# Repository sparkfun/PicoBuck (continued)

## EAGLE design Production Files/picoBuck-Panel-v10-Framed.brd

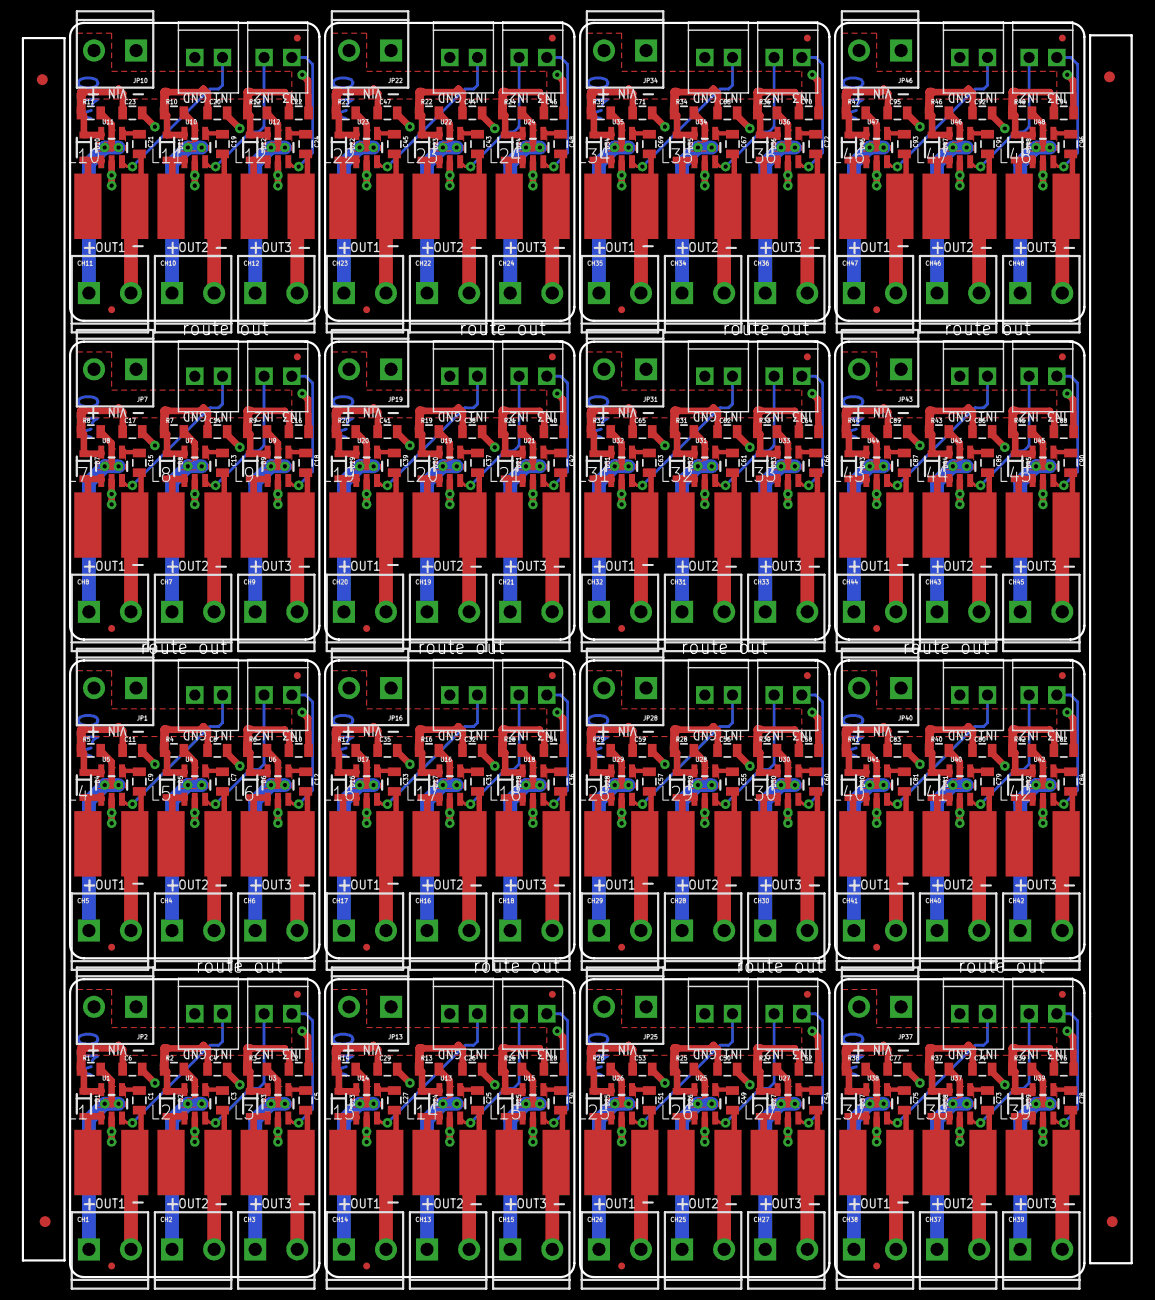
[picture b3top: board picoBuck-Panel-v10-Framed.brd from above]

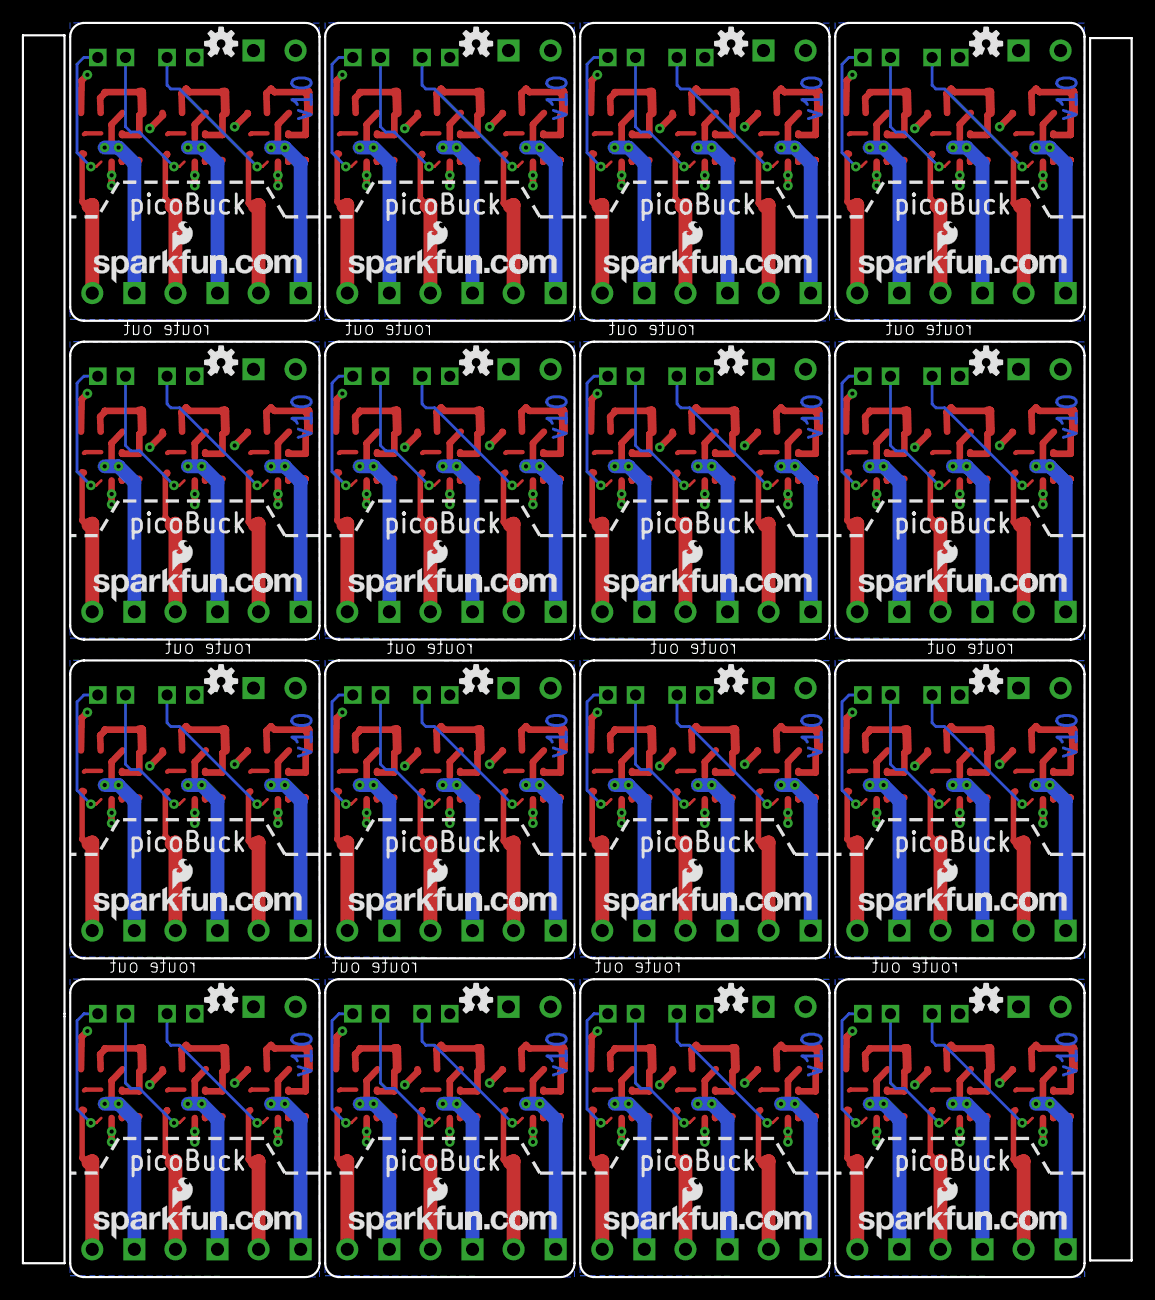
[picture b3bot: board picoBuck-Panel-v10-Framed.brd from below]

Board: 2 copper layers, 101.6 x 114.9 mm, 452 parts (32 on the bottom side), 224 nets.

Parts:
C1, C3, C5, C7, C9, C12, C13, C15, C18, C19, C21, C24, C25, C27, C30, C31, C33, C36, C37, C39, C42, C43, C45, C48, C49, C51, C54, C55, C57, C60, C61, C63, C66, C67, C69, C72, C73, C75, C78, C79, C81, C84, C85, C87, C90, C91, C93, C96: 1uF; 0805
C2, C4, C6, C8, C10, C11, C14, C16, C17, C20, C22, C23, C26, C28, C29, C32, C34, C35, C38, C40, C41, C44, C46, C47, C50, C52, C53, C56, C58, C59, C62, C64, C65, C68, C70, C71, C74, C76, C77, C80, C82, C83, C86, C88, C89, C92, C94, C95: 2.2uF; 0805
CH1, CH2, CH3, CH4, CH5, CH6, CH7, CH8, CH9, CH10, CH11, CH12, CH13, CH14, CH15, CH16, CH17, CH18, CH19, CH20, CH21, CH22, CH23, CH24, CH25, CH26, CH27, CH28, CH29, CH30, CH31, CH32, CH33, CH34, CH35, CH36, CH37, CH38, CH39, CH40, CH41, CH42, CH43, CH44, CH45, CH46, CH47, CH48: SCREWTERMINAL-3.5MM-2_LOCK
D1, D2, D3, D4, D5, D6, D7, D8, D9, D10, D11, D12, D13, D14, D15, D16, D17, D18, D19, D20, D21, D22, D23, D24, D25, D26, D27, D28, D29, D30, D31, D32, D33, D34, D35, D36, D37, D38, D39, D40, D41, D42, D43, D44, D45, D46, D47, D48: BAT20JFILM; SOD-323
E$1, E$2, E$3, E$4: FIDUCIAL-1X2
FID1, FID2, FID3, FID4, FID5, FID6, FID7, FID8, FID9, FID10, FID11, FID12, FID13, FID14, FID15, FID16, FID17, FID18, FID19, FID20, FID21, FID22, FID23, FID24, FID25, FID26, FID27, FID28, FID29, FID30, FID31, FID32: FIDUCIALUFIDUCIAL; MICRO-FIDUCIAL
JP1, JP2, JP7, JP10, JP13, JP16, JP19, JP22, JP25, JP28, JP31, JP34, JP37, JP40, JP43, JP46: SCREWTERMINAL-3.5MM-2_LOCK
JP3, JP4, JP5, JP6, JP8, JP9, JP11, JP12, JP14, JP15, JP17, JP18, JP20, JP21, JP23, JP24, JP26, JP27, JP29, JP30, JP32, JP33, JP35, JP36, JP38, JP39, JP41, JP42, JP44, JP45, JP47, JP48: M022.54MM_SCREWTERM; 1X02_2.54_SCREWTERM
L1, L2, L3, L4, L5, L6, L7, L8, L9, L10, L11, L12, L13, L14, L15, L16, L17, L18, L19, L20, L21, L22, L23, L24, L25, L26, L27, L28, L29, L30, L31, L32, L33, L34, L35, L36, L37, L38, L39, L40, L41, L42, L43, L44, L45, L46, L47, L48: 33uH; SRN6045
LOGO1, LOGO3, LOGO5, LOGO7, LOGO9, LOGO11, LOGO13, LOGO15, LOGO17, LOGO19, LOGO21, LOGO23, LOGO25, LOGO27, LOGO29, LOGO31: OSHW-LOGOS; OSHW-LOGO-S
LOGO2, LOGO4, LOGO6, LOGO8, LOGO10, LOGO12, LOGO14, LOGO16, LOGO18, LOGO20, LOGO22, LOGO24, LOGO26, LOGO28, LOGO30, LOGO32: LOGO-SFENEW; SFE-NEW-WEBLOGO
R1, R2, R3, R4, R5, R6, R7, R8, R9, R10, R11, R12, R13, R14, R15, R16, R17, R18, R19, R20, R21, R22, R23, R24, R25, R26, R27, R28, R29, R30, R31, R32, R33, R34, R35, R36, R37, R38, R39, R40, R41, R42, R43, R44, R45, R46, R47, R48: 0.3R; 0805
U1, U2, U3, U4, U5, U6, U7, U8, U9, U10, U11, U12, U13, U14, U15, U16, U17, U18, U19, U20, U21, U22, U23, U24, U25, U26, U27, U28, U29, U30, U31, U32, U33, U34, U35, U36, U37, U38, U39, U40, U41, U42, U43, U44, U45, U46, U47, U48: SOT23-5

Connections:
CTRL_CH1: JP4.P1, U1.3
CTRL_CH2: JP3.P2, U2.3
CTRL_CH3: JP3.P1, U3.3
CTRL_CH4: JP6.P1, U5.3
CTRL_CH5: JP5.P2, U4.3
CTRL_CH6: JP5.P1, U6.3
CTRL_CH7: JP9.P1, U8.3
CTRL_CH8: JP8.P2, U7.3
CTRL_CH9: JP8.P1, U9.3
CTRL_CH10: JP12.P1, U11.3
CTRL_CH11: JP11.P2, U10.3
CTRL_CH12: JP11.P1, U12.3
CTRL_CH13: JP15.P1, U14.3
CTRL_CH14: JP14.P2, U13.3
CTRL_CH15: JP14.P1, U15.3
CTRL_CH16: JP18.P1, U17.3
CTRL_CH17: JP17.P2, U16.3
CTRL_CH18: JP17.P1, U18.3
CTRL_CH19: JP21.P1, U20.3
CTRL_CH20: JP20.P2, U19.3
CTRL_CH21: JP20.P1, U21.3
CTRL_CH22: JP24.P1, U23.3
CTRL_CH23: JP23.P2, U22.3
CTRL_CH24: JP23.P1, U24.3
CTRL_CH25: JP27.P1, U26.3
CTRL_CH26: JP26.P2, U25.3
CTRL_CH27: JP26.P1, U27.3
CTRL_CH28: JP30.P1, U29.3
CTRL_CH29: JP29.P2, U28.3
CTRL_CH30: JP29.P1, U30.3
CTRL_CH31: JP33.P1, U32.3
CTRL_CH32: JP32.P2, U31.3
CTRL_CH33: JP32.P1, U33.3
CTRL_CH34: JP36.P1, U35.3
CTRL_CH35: JP35.P2, U34.3
CTRL_CH36: JP35.P1, U36.3
CTRL_CH37: JP39.P1, U38.3
CTRL_CH38: JP38.P2, U37.3
CTRL_CH39: JP38.P1, U39.3
CTRL_CH40: JP42.P1, U41.3
CTRL_CH41: JP41.P2, U40.3
CTRL_CH42: JP41.P1, U42.3
CTRL_CH43: JP45.P1, U44.3
CTRL_CH44: JP44.P2, U43.3
CTRL_CH45: JP44.P1, U45.3
CTRL_CH46: JP48.P1, U47.3
CTRL_CH47: JP47.P2, U46.3
CTRL_CH48: JP47.P1, U48.3
GND: C2.2, C4.2, C6.2, JP2.1, JP4.P2, U1.2, U2.2, U3.2
GND1: C8.2, C10.2, C11.2, JP1.1, JP6.P2, U4.2, U5.2, U6.2
GND2: C14.2, C16.2, C17.2, JP7.1, JP9.P2, U7.2, U8.2, U9.2
GND3: C20.2, C22.2, C23.2, JP10.1, JP12.P2, U10.2, U11.2, U12.2
GND4: C26.2, C28.2, C29.2, JP13.1, JP15.P2, U13.2, U14.2, U15.2
GND5: C32.2, C34.2, C35.2, JP16.1, JP18.P2, U16.2, U17.2, U18.2
GND6: C38.2, C40.2, C41.2, JP19.1, JP21.P2, U19.2, U20.2, U21.2
GND7: C44.2, C46.2, C47.2, JP22.1, JP24.P2, U22.2, U23.2, U24.2
GND8: C50.2, C52.2, C53.2, JP25.1, JP27.P2, U25.2, U26.2, U27.2
GND9: C56.2, C58.2, C59.2, JP28.1, JP30.P2, U28.2, U29.2, U30.2
GND10: C62.2, C64.2, C65.2, JP31.1, JP33.P2, U31.2, U32.2, U33.2
GND11: C68.2, C70.2, C71.2, JP34.1, JP36.P2, U34.2, U35.2, U36.2
GND12: C74.2, C76.2, C77.2, JP37.1, JP39.P2, U37.2, U38.2, U39.2
GND13: C80.2, C82.2, C83.2, JP40.1, JP42.P2, U40.2, U41.2, U42.2
GND14: C86.2, C88.2, C89.2, JP43.1, JP45.P2, U43.2, U44.2, U45.2
GND15: C92.2, C94.2, C95.2, JP46.1, JP48.P2, U46.2, U47.2, U48.2
IND1-1: D1.2, L1.1, U1.1
IND1-2: D4.2, L4.1, U5.1
IND1-3: D7.2, L7.1, U8.1
IND1-4: D10.2, L10.1, U11.1
IND1-5: D13.2, L13.1, U14.1
IND1-6: D16.2, L16.1, U17.1
IND1-7: D19.2, L19.1, U20.1
IND1-8: D22.2, L22.1, U23.1
IND1-9: D25.2, L25.1, U26.1
IND1-10: D28.2, L28.1, U29.1
IND1-11: D31.2, L31.1, U32.1
IND1-12: D34.2, L34.1, U35.1
IND1-13: D37.2, L37.1, U38.1
IND1-14: D40.2, L40.1, U41.1
IND1-15: D43.2, L43.1, U44.1
IND1-16: D46.2, L46.1, U47.1
IND2-1: D2.2, L2.1, U2.1
IND2-2: D5.2, L5.1, U4.1
IND2-3: D8.2, L8.1, U7.1
IND2-4: D11.2, L11.1, U10.1
IND2-5: D14.2, L14.1, U13.1
IND2-6: D17.2, L17.1, U16.1
IND2-7: D20.2, L20.1, U19.1
IND2-8: D23.2, L23.1, U22.1
IND2-9: D26.2, L26.1, U25.1
IND2-10: D29.2, L29.1, U28.1
IND2-11: D32.2, L32.1, U31.1
IND2-12: D35.2, L35.1, U34.1
IND2-13: D38.2, L38.1, U37.1
IND2-14: D41.2, L41.1, U40.1
IND2-15: D44.2, L44.1, U43.1
IND2-16: D47.2, L47.1, U46.1
IND3-1: D3.2, L3.1, U3.1
IND3-2: D6.2, L6.1, U6.1
IND3-3: D9.2, L9.1, U9.1
IND3-4: D12.2, L12.1, U12.1
IND3-5: D15.2, L15.1, U15.1
IND3-6: D18.2, L18.1, U18.1
IND3-7: D21.2, L21.1, U21.1
IND3-8: D24.2, L24.1, U24.1
IND3-9: D27.2, L27.1, U27.1
IND3-10: D30.2, L30.1, U30.1
IND3-11: D33.2, L33.1, U33.1
IND3-12: D36.2, L36.1, U36.1
IND3-13: D39.2, L39.1, U39.1
IND3-14: D42.2, L42.1, U42.1
IND3-15: D45.2, L45.1, U45.1
IND3-16: D48.2, L48.1, U48.1
unnamed: C7.2, CH4.2, L5.2
unnamed: C7.1, CH4.1, R4.2, U4.4
unnamed: C9.2, CH5.2, L4.2
unnamed: C9.1, CH5.1, R5.2, U5.4
unnamed: C1.2, CH1.2, L1.2
unnamed: C12.2, CH6.2, L6.2
unnamed: C12.1, CH6.1, R6.2, U6.4
unnamed: C13.2, CH7.2, L8.2
unnamed: C3.2, CH2.2, L2.2
unnamed: C13.1, CH7.1, R7.2, U7.4
unnamed: C1.1, CH1.1, R1.2, U1.4
unnamed: C15.2, CH8.2, L7.2
unnamed: C3.1, CH2.1, R2.2, U2.4
unnamed: C15.1, CH8.1, R8.2, U8.4
unnamed: C18.2, CH9.2, L9.2
unnamed: C5.2, CH3.2, L3.2
unnamed: C18.1, CH9.1, R9.2, U9.4
unnamed: C5.1, CH3.1, R3.2, U3.4
unnamed: C19.2, CH10.2, L11.2
unnamed: C19.1, CH10.1, R10.2, U10.4
unnamed: C21.2, CH11.2, L10.2
unnamed: C21.1, CH11.1, R11.2, U11.4
unnamed: C24.2, CH12.2, L12.2
unnamed: C24.1, CH12.1, R12.2, U12.4
unnamed: C25.2, CH13.2, L14.2
unnamed: C25.1, CH13.1, R13.2, U13.4
unnamed: C27.2, CH14.2, L13.2
unnamed: C27.1, CH14.1, R14.2, U14.4
unnamed: C30.2, CH15.2, L15.2
unnamed: C30.1, CH15.1, R15.2, U15.4
unnamed: C31.2, CH16.2, L17.2
unnamed: C31.1, CH16.1, R16.2, U16.4
unnamed: C33.2, CH17.2, L16.2
unnamed: C33.1, CH17.1, R17.2, U17.4
unnamed: C36.2, CH18.2, L18.2
unnamed: C36.1, CH18.1, R18.2, U18.4
unnamed: C37.2, CH19.2, L20.2
unnamed: C37.1, CH19.1, R19.2, U19.4
unnamed: C39.2, CH20.2, L19.2
unnamed: C39.1, CH20.1, R20.2, U20.4
unnamed: C42.2, CH21.2, L21.2
unnamed: C42.1, CH21.1, R21.2, U21.4
unnamed: C43.2, CH22.2, L23.2
unnamed: C43.1, CH22.1, R22.2, U22.4
unnamed: C45.2, CH23.2, L22.2
unnamed: C45.1, CH23.1, R23.2, U23.4
unnamed: C48.2, CH24.2, L24.2
unnamed: C48.1, CH24.1, R24.2, U24.4
unnamed: C49.2, CH25.2, L26.2
unnamed: C49.1, CH25.1, R25.2, U25.4
unnamed: C51.2, CH26.2, L25.2
unnamed: C51.1, CH26.1, R26.2, U26.4
unnamed: C54.2, CH27.2, L27.2
unnamed: C54.1, CH27.1, R27.2, U27.4
unnamed: C55.2, CH28.2, L29.2
unnamed: C55.1, CH28.1, R28.2, U28.4
unnamed: C57.2, CH29.2, L28.2
unnamed: C57.1, CH29.1, R29.2, U29.4
unnamed: C60.2, CH30.2, L30.2
unnamed: C60.1, CH30.1, R30.2, U30.4
unnamed: C61.2, CH31.2, L32.2
unnamed: C61.1, CH31.1, R31.2, U31.4
unnamed: C63.2, CH32.2, L31.2
unnamed: C63.1, CH32.1, R32.2, U32.4
unnamed: C66.2, CH33.2, L33.2
unnamed: C66.1, CH33.1, R33.2, U33.4
unnamed: C67.2, CH34.2, L35.2
unnamed: C67.1, CH34.1, R34.2, U34.4
unnamed: C69.2, CH35.2, L34.2
unnamed: C69.1, CH35.1, R35.2, U35.4
unnamed: C72.2, CH36.2, L36.2
unnamed: C72.1, CH36.1, R36.2, U36.4
unnamed: C73.2, CH37.2, L38.2
unnamed: C73.1, CH37.1, R37.2, U37.4
unnamed: C75.2, CH38.2, L37.2
unnamed: C75.1, CH38.1, R38.2, U38.4
unnamed: C78.2, CH39.2, L39.2
unnamed: C78.1, CH39.1, R39.2, U39.4
unnamed: C79.2, CH40.2, L41.2
unnamed: C79.1, CH40.1, R40.2, U40.4
unnamed: C81.2, CH41.2, L40.2
unnamed: C81.1, CH41.1, R41.2, U41.4
unnamed: C84.2, CH42.2, L42.2
unnamed: C84.1, CH42.1, R42.2, U42.4
unnamed: C85.2, CH43.2, L44.2
unnamed: C85.1, CH43.1, R43.2, U43.4
unnamed: C87.2, CH44.2, L43.2
unnamed: C87.1, CH44.1, R44.2, U44.4
unnamed: C90.2, CH45.2, L45.2
unnamed: C90.1, CH45.1, R45.2, U45.4
unnamed: C91.2, CH46.2, L47.2
unnamed: C91.1, CH46.1, R46.2, U46.4
unnamed: C93.2, CH47.2, L46.2
unnamed: C93.1, CH47.1, R47.2, U47.4
unnamed: C96.2, CH48.2, L48.2
unnamed: C96.1, CH48.1, R48.2, U48.4
VIN: C2.1, C4.1, C6.1, D1.1, D2.1, D3.1, JP2.2, R1.1, R2.1, R3.1, U1.5, U2.5, U3.5
VIN1: C8.1, C10.1, C11.1, D4.1, D5.1, D6.1, JP1.2, R4.1, R5.1, R6.1, U4.5, U5.5, U6.5
VIN2: C14.1, C16.1, C17.1, D7.1, D8.1, D9.1, JP7.2, R7.1, R8.1, R9.1, U7.5, U8.5, U9.5
VIN3: C20.1, C22.1, C23.1, D10.1, D11.1, D12.1, JP10.2, R10.1, R11.1, R12.1, U10.5, U11.5, U12.5
VIN4: C26.1, C28.1, C29.1, D13.1, D14.1, D15.1, JP13.2, R13.1, R14.1, R15.1, U13.5, U14.5, U15.5
VIN5: C32.1, C34.1, C35.1, D16.1, D17.1, D18.1, JP16.2, R16.1, R17.1, R18.1, U16.5, U17.5, U18.5
VIN6: C38.1, C40.1, C41.1, D19.1, D20.1, D21.1, JP19.2, R19.1, R20.1, R21.1, U19.5, U20.5, U21.5
VIN7: C44.1, C46.1, C47.1, D22.1, D23.1, D24.1, JP22.2, R22.1, R23.1, R24.1, U22.5, U23.5, U24.5
VIN8: C50.1, C52.1, C53.1, D25.1, D26.1, D27.1, JP25.2, R25.1, R26.1, R27.1, U25.5, U26.5, U27.5
VIN9: C56.1, C58.1, C59.1, D28.1, D29.1, D30.1, JP28.2, R28.1, R29.1, R30.1, U28.5, U29.5, U30.5
VIN10: C62.1, C64.1, C65.1, D31.1, D32.1, D33.1, JP31.2, R31.1, R32.1, R33.1, U31.5, U32.5, U33.5
VIN11: C68.1, C70.1, C71.1, D34.1, D35.1, D36.1, JP34.2, R34.1, R35.1, R36.1, U34.5, U35.5, U36.5
VIN12: C74.1, C76.1, C77.1, D37.1, D38.1, D39.1, JP37.2, R37.1, R38.1, R39.1, U37.5, U38.5, U39.5
VIN13: C80.1, C82.1, C83.1, D40.1, D41.1, D42.1, JP40.2, R40.1, R41.1, R42.1, U40.5, U41.5, U42.5
VIN14: C86.1, C88.1, C89.1, D43.1, D44.1, D45.1, JP43.2, R43.1, R44.1, R45.1, U43.5, U44.5, U45.5
VIN15: C92.1, C94.1, C95.1, D46.1, D47.1, D48.1, JP46.2, R46.1, R47.1, R48.1, U46.5, U47.5, U48.5

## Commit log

2013-04-30 Bringing board layout up to SparkFun DRC compliance
2013-04-30 Bringing up to standards- submitting this for review
2013-04-30 Added version number text
2013-05-06 Tweaks on text positions.
2013-06-25 Update to v10, for release. Add .gitignore and README
2013-06-25 Cosmetic tweaks
    moved brd on grid, shrunk ground plane, other minor stuff
2013-06-25 Production ready
    panelized and added fiducials
2013-06-27 Modified panel
    to prevent silkscreen outlines from hanging over onto adjacent boards.
2013-08-27 Updating README
2013-08-27 Update README.md
    Adding basic description of part.
2015-07-02 High power initial revision - added 2nd sense resistor and solder jumper - changed diode to higher voltage version - changed input cap to higher voltage version
2015-07-07 Fixed changes from femtobuck feedback
2015-07-07 Make files as they were before I started monkeying with them
2015-07-07 Updated library for some silk changes
2015-07-08 Add vin range to sch
2015-07-29 Fixed issues from qc feedback
2015-09-14 Added some silk to back of board
2015-09-15 Center text on center screw term, add gnd symbols to JP4/5
2015-09-16 Adjusted upper dim line for panelization
2015-09-17 created panel v12
2022-03-03 AL8805 buck LED driver EOL, replace with AL8860
    * Replaced AL8805 with AL8860 drop in replacement
    * Bumped version number on board and schematic
    * Created schematic pdf and zip folder of eagle files for the product page
2025-06-27 Update README.md
    Updating link
